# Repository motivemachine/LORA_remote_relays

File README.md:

# Lora Remote Relays

AC powered relay control board using Lora radios. Turn on lights, heaters or anything else you need at a distance.
The first one has been installed and running smooth for several months now! Check it out here: https://asthemillturns.serveblog.net/lora-ac-relays.html

## Notice about AC and relays!
##### Build at your own risk.
This devices runs on 110VAC, and controls other 110VAC devices. Do not make this if you don't know what you're doing! Power traces are very conservatively rated at 8 amp total (both relays combined), further changes and testing should increase this. There is no snubber circuity on the relays, so as-is should only be used with resistive loads (lights, heaters, etc.). Small fans should be fine. Running motors should have proper circuitry in place on the relay outputs to handle any noise or back-EMF from such devices.

## Project status
Board design and code for v1.1 is completed and all is running well. Board v1.2 design is complete but code has not been written yet. Code for v1.1 should work almost as-is after changing the pin numbers. Primarily the difference between 1.1 and 1.2 is that 1.1 must poll the radio for new packets while the new version will use interrupts. Other changes are improved silkscreening and more IO breakouts for other projects.

## Pinout description

I've broken out some extra arduino pins for integration in future projects. Starting from the upper left:
  * The first three pins from upper-left down are 5 volts, Analog 1, and ground. This was originally used for a TMP36 analog temperature sensor. This would also work with any of the Dallas One-wire digital temperature sensors.
  * Next we have a terminal block with Ground, analog 4 and analog 5. My purpose for these is to include some external on/off switches for the relays. Could be handy to turn the lights on manually when already standing next to them. The terminal block
  * Final four pins are ground, analog 6, analog 7, and 5 volts. These are just for future projects and could be used for more external sensors, switches, or status LEDs
  * To the lower right of the Nano the serial pins are exposed for future ideas.

## Completed board
This is a photo of the complete v1.1 board. The schematics are up to date with v1.2, which adds some extra IO pins, adjusted silkscreen, and moved some parts to make them easier to work with (like moving the fuse holder farther away from the relays)

## Usage/code description
There are two PlatformIO project folders, one for the main program, one named 'circuit test'. The circuit test routing just verifies everything was connected correctly: blink leds, toggle relays, send a packet. Both programs are contained in the 'src/' folder and can be pulled from there if you wish to use the code with Arduino IDE.

Some of these software functions are in a state of change as I figure out how best to integrate these devices with my Lora home network, but the basic purpose remains the same:
  * Set local(self) and destination radio addresses (in the form of a byte in Hex format)
      * Destination address is read from the dip switches on startup. Simply make sure these are the same across all boards. In this case it is the address of the Lora radio on the Raspberry Pi that controls everything.
      * If the button is held on startup (or while the arduino nano reset button is pressed) blink the LEDs while in the 'set local address' function. Set the dip switches *different* on each board so each one can be uniquely addressed by whatever device you have turning the relays on and off. Press button again to write this new address to EEPROM.
  * Receive message on which relay to turn on or off
    * Currently this just listens for a message to the local address and a 2 index array of zeros and ones (i.e [1,0]). First element is what the first relay state should be, second is what the second relay state should be.
  * Reply with ACK after processing the previous message, or respond with current relay states when asked
    * This isn't quite complete yet but the plan is to implement a proper ack/nack response for more reliable operation.
    * The second thing is to reply to the message 'STAT' with the current status of both relays. The thinking is any one control device may turn the relays on and off, but it would be nice of other control devices could later know what their status is without toggling anything on or off. This also lets a controller know that a specific board is, in fact, online and reachable.

## TODO

- [ ] Create and upload a proper BOM
- [x] Finish and debug 'status' functions
- [ ] Further testing of board temperature rise at high currents
- [ ] Change from polling loop to pin-change interrupt
- [x] Clean up lots of old comments, debug info and test functions
- [x] Add watchdog timer for protection from random hangups.

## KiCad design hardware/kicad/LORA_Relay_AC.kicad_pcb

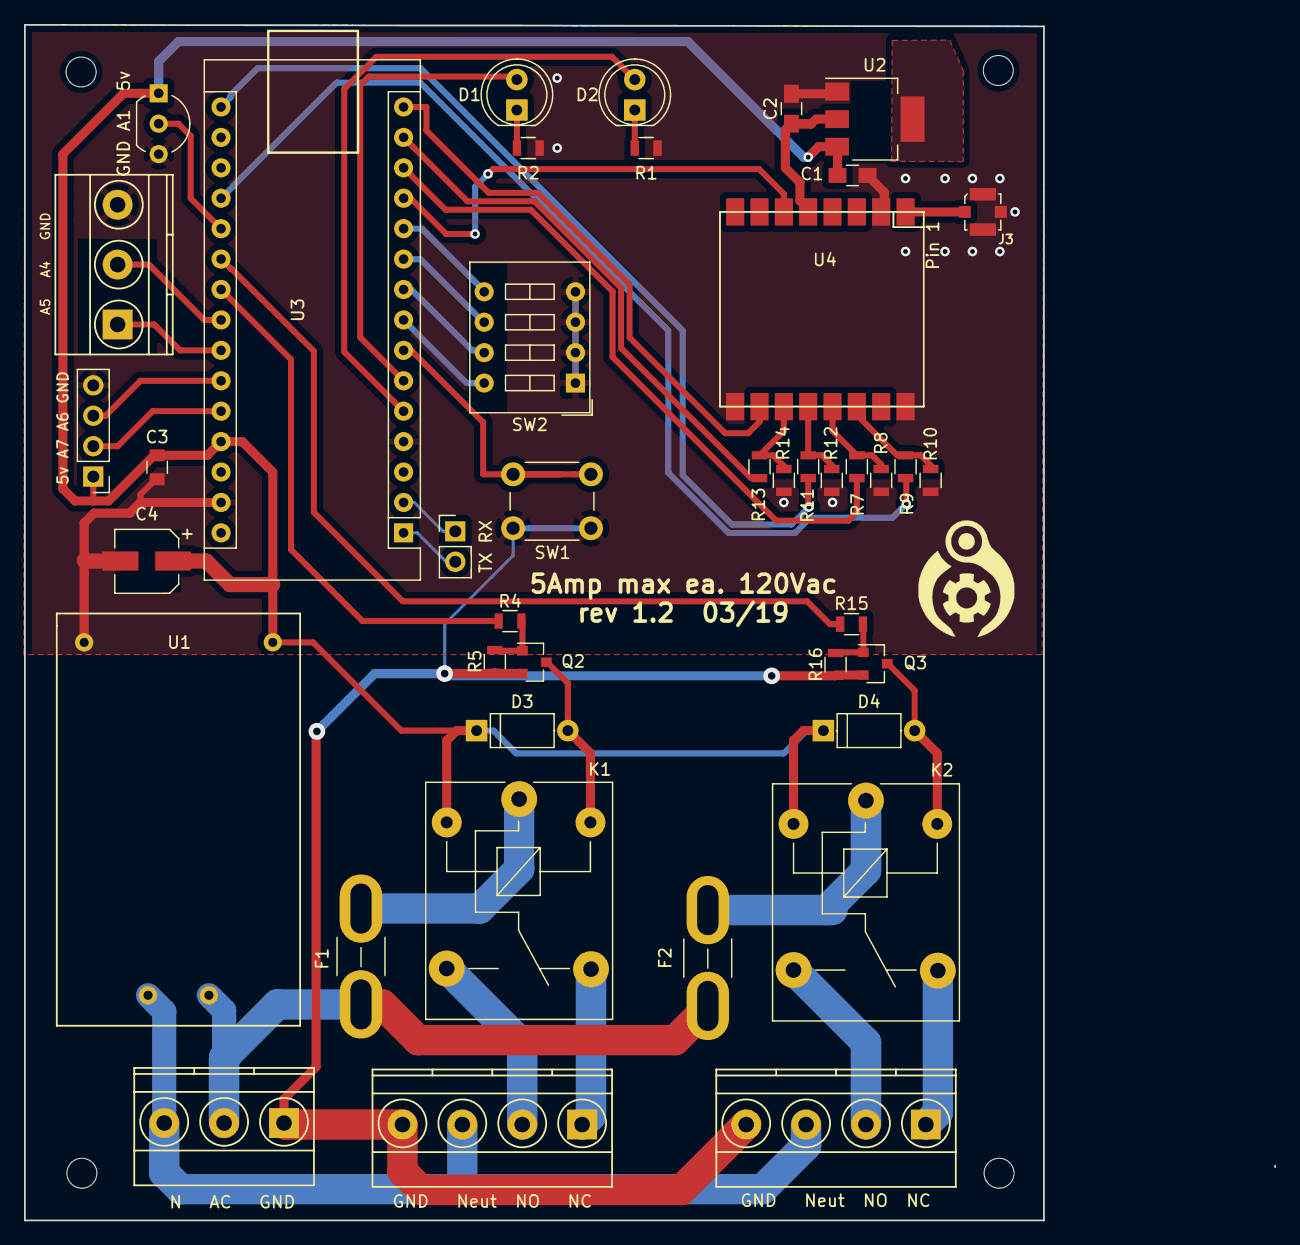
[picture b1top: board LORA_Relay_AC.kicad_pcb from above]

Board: 2 copper layers, 104.4 x 99.8 mm, 46 parts (0 on the bottom side), 44 nets.

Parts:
5v A7 A6 GND: gpio; PinHeader_1x04_P2.54mm_Vertical
A5   A4   GND: external_Sw; TerminalBlock_Phoenix_MKDS1.5-3pol
C1: 1uf; C_0805_HandSoldering
C2: 22uf; C_0805_HandSoldering
C3: .1uf; C_0805
C4: 100uf; CP_Elec_5x5.3
D1, D2: LED; LED_D5.0mm
D3, D4: 4001; D_A-405_P7.62mm_Horizontal
F1, F2: Fuse; BladeFuse-Mini
GND   Neut  NO   NC: relay1; TerminalBlock_Phoenix_MKDS1.5-4pol
GND   Neut  NO  NC: relay2; TerminalBlock_Phoenix_MKDS1.5-4pol
GND A1  5v: tmp36; TO-92_Inline_Wide
H1, H2, H3, H4: MountingHole; MountingHole_2.5mm
J3: IPX; Molex_Microcoaxial_RF
K1: relay1; Relay_SPDT_SANYOU_SRD_Series_Form_C
K2: relay2; Relay_SPDT_SANYOU_SRD_Series_Form_C
N   AC   GND: ACin; TerminalBlock_Phoenix_MKDS1.5-3pol
Q2, Q3: MMBT3904; SOT-23
R1, R2: 3k3; R_0805
R4, R15: 100; R_0805
R5, R16: 10k; R_0805
R7, R9, R11, R13: 1k; R_0805
R8, R10, R12, R14: 2k; R_0805
SW1: SW_Push; SW_PUSH_6mm_h4.3mm
SW2: SW_DIP_x04; SW_DIP_x4_W7.62mm_Slide
TX RX: Serial; PinHeader_1x02_P2.54mm_Vertical
U1: HLK-PM01
U2: AMS1117-3.3; SOT-223-3_TabPin2
U3: ArduinoNano
U4: Sx1278_LORA_Module; LORA_SX1278_Module

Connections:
+3V3: C2.1, U2.2, U4.5
+5V: 5v A7 A6 GND.1, C1.1, C3.1, C4.1, D3.1, D4.1, GND A1 5v.1, K1.A1, K2.A1, U1.4, U2.3, U3.+5V
/irq: U3.9, U4.6
/lora_cs: R7.2, U3.10
/lora_rst: R9.2, U3.ADC0
/relay1: R4.2, U3.ADC3
/relay2: R15.2, U3.ADC2
Earth: 5v A7 A6 GND.4, A5 A4 GND.3, C1.2, C2.2, C3.2, C4.2, GND Neut NO NC.4, GND Neut NO NC.4, GND A1 5v.3, J3.2, N AC GND.1, Q2.2, Q3.2, R1.2, R2.2, R5.1, R8.2, R10.2, R12.2, R14.2, R16.1, SW1.1, SW2.1, SW2.2, SW2.3, SW2.4, U1.3, U2.1, U3.gnd, U4.2, U4.9, U4.16
NEUT: GND Neut NO NC.3, GND Neut NO NC.3, N AC GND.2, U1.1
unnamed: D1.1, R2.1
unnamed: D1.2, U3.3
unnamed: D2.1, R1.1
unnamed: D2.2, U3.2
unnamed: D3.2, K1.A2, Q2.3
unnamed: D4.2, K2.A2, Q3.3
unnamed: F1.1, K1.11
unnamed: F2.1, K2.11
unnamed: GND Neut NO NC.1, K1.12
unnamed: GND Neut NO NC.2, K1.14
unnamed: J3.1, U4.1
unnamed: 5v A7 A6 GND.2, U3.ADC7
unnamed: 5v A7 A6 GND.3, U3.ADC6
unnamed: GND Neut NO NC.1, K2.12
unnamed: GND Neut NO NC.2, K2.14
unnamed: TX RX.1, U3.rx
unnamed: TX RX.2, U3.tx
unnamed: GND A1 5v.2, U3.ADC1
unnamed: A5 A4 GND.1, U3.ADC5
unnamed: A5 A4 GND.2, U3.ADC4
unnamed: Q2.1, R4.1, R5.2
unnamed: Q3.1, R15.1, R16.2
unnamed: R7.1, R8.1, U4.13
unnamed: R9.1, R10.1, U4.14
unnamed: R11.1, R12.1, U4.12
unnamed: R13.1, R14.1, U4.11
unnamed: SW1.2, U3.4
unnamed: SW2.5, U3.8
unnamed: SW2.6, U3.7
unnamed: SW2.7, U3.6
unnamed: SW2.8, U3.5
VAC: F1.2, F2.2, N AC GND.3, U1.2
miso: U3.12, U4.10
mosi: R13.2, U3.11
sck: R11.2, U3.13

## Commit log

2019-06-24 upload kicad and gerbers
2019-06-24 upload circuit test program
2019-06-24 upload readme
2019-06-25 add pinout graphic
2019-07-03 upload pictures
2019-08-17 rework 1.1 code, add more docs
2020-03-12 cleanup and debug rx hanging
2020-03-13 add watchdog timer fallback
2020-03-14 fixed watchdog mistake, fixing SPI issues
2020-03-27 cleanup unused/debug functions
2020-03-27 Add new file
2020-06-03 pinout fix
